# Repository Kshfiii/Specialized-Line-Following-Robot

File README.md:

# Specialized-Line-Following-Robot

This is a specialized line follower robot with a custom built 8 Sensor Array, using tcrt5000 IR sensors, for sensing the lines. In addition to basic line following, the robot has a specialized function for dispensing pellets into designated spots, at different heights, for which it uses a scissor lift along with a conveyor belt system, powered by high torque n20 motors. It was made to compete in a robotics competition, NERC, and as a way to challenge myself to make a better LFR then the one I made before, which I think I have.

## About

<!-- This Project is powered by an 11.1v 3300 mah Li-po battery. It has 3 power rails; 11.1v, 5v, and <!- 3rd power line here ->, it uses two mini mp2307 to convert the voltages.-->
### 1. Robot function 

The robot follows a 3cm wide black line on the arena floor, maneuvering intersections & Zig Zag patterns on the arena floor. At Storage rack 1 (S1), a box of 7x7 inches supports the storage rack, with one of four faces colored blue. the robot must go around the box to detect the blue colored face, where the slot openings are present in the form of a 2x2 grid, as seen in the image above. The robot must detect strips below the slots as either blue or red, placing the pellets into the slots marked blue, and skipping over the red ones. The robot then heads to Storage rack 2 (S2), repeating the same procedure. Then, the robot travels through the zig zag pattern and climbs a ramp to reach Storage rack 3 (S3), After sucessful dispensing into designated slots at S3, it parks itself beyond the red line. 

### 2. Body
The body consists of three layers. The Base, the Middle, and the top most layer. 
 #### 2.1 The Base

The base is made of a custom 3d printed Chasis, housing four GA25-370 Motors and a battery on top with the IR Sensor Array Mounted to the bottom, Alongside extruded platforms for inserts.

##### 2.1.1 IR Sensor Array

<!-- add ss of 3d model from kicad & schematics-->
A custom built 8 channel analog IR sensor array bulit from tcrt5000 sensors. It uses 4.7k & 1k resistors. It also utilizes capacitors & an led that lights up when a sensor is returning a reading, serving as a checker to see if it works. 

#### 2.2 The Middle layer

<!-- add ss of middle layer from onshape, make a banner thing with lables in canva and put it here, layer has, acrylic base, spacers, pcb, hcsr04  -->
The Middle layer is supported by a laser cut acrylic sheet which is screwed on top of the 3d printed chasis using spacers. It consists of a custom built PCB & spacers along with the HC-SR04 ultrasonic sensor for distance measurement. 

##### 2.2.1 PCB

The pcb routes a 3300mah, 11.1v li-po battery pack through two mini MP2307 buck convertor, forming 3 power rails, 11.1v, 5v, and <!-- x volts --> which are used throughout the robot. The PCB houses the STM32F401 Microcontroller with two TB6612FNG motor driver breakout boards, one of which governs the motion of the GA25-370 motors and the other controls the N20 motors used for raising the scissor lift and moving the conveyor belt. It has headers for the IR sensors and the ultrasonic sensor.

#### 2.3 The Top layer

The top layer is also supported by a laser cut acrylic sheet which is screwed on top of the first acrylic sheet, separated by ~1.2in vertically, using spacers and nuts. It is home to the whole Pellet dispensing mechanism, The scissor lift, the Color sensing system and the conveyor belt.

##### 2.3.1 Scissor lift
<!-- add ss of 3d model from onshape, make a banner thing with lables in canva and put it here -->
The scissor lift is made entriely of a 3d printed body. It's movement is controlled by a high torque N20 gear motor which sits on the acrylic sheet. The collapsed height of the lift is <!-- x inches --> and it can streatch upto <!-- y inches --> 

##### 2.3.2 Color sensing system
<!-- add ss of 3d model from onshape, make a banner thing with lables in canva and put it here -->
The color sensing system consists of a Sg90 servo with a TCS34725 color sensor mounted to a 3d printed arm, which is screwed onto Sg90. The arm is <!-- z inches --> in length. The system is fixed underneath the top plate of the scissor lift, so that it can climb with the lift, giving it the ability to detect the color of the strips at both heights vertically. The servo rotates the arm 180° which allows the color sensor to detect both heights laterally. By using this system, the color sensor can cover the strips below each slot in the 2x2 grid.

##### 2.3.3 Conveyor belt
<!-- add ss of 3d model from onshape with the pellets stored and dimensions, make a banner thing with lables in canva and put it here -->
The conveyor belt is made of a 3d printed body. It uses a high torque N20 motor and bearings to rotate the pulleys, which drive the belt. The pellets sit on top of the belt, preloaded before the robot starts. 

## Assembly & Building
Go to [Onshape](https://cad.onshape.com/documents/1d0c454716dc1fb7909d87f9/w/77de741c5d18967e566ddcde/e/cc4241ede1b87dd95ef516c6?renderMode=0&uiState=6a198c15967ad61ab2482240) Each part of the Line follower robot has been organized into folders. All print parts are consolidated in the 'To Print' tab on the bottom left. If confusion persists, you may contact me at: kasshafemman@gmail.com. Now follow along for each section.

### Body
Open the LFR Body Folder to see the CAD model. Now, using the brackets, fix the motors to the chasis. Put the wheels on the motor shaft. Put the insrts into the extruded square, then use it to screw Acrylic layer one. Put the PCB on this layer and the Ultrasonic sensor, within its bracket. Add a spacer and screw in Acrylic layer 2. Then put the scissor lift's extruded patterns (for the lack of a better word) on top of the complimentary slots on Acrylic layer 2.

### Scissor Lift:
Open Scissor lift folder for reference. Slide the scissor legs onto the shafts and put them in the place holders made on platform one. Use a string or pice of yarn, tying one end to the n20 motor and the other to the center of shaft 2. To prevent the shafts from sliding off, attach the knubs to the shaft's complementery ends. Now put pin 1 through one end of the hole in the scissor leg and pin 2 through the other, repeat this for all the arms to get the scissors pattern as shown in the assembly.

### Conveyor Belt
Open conveyor belt folder for reference. Put the supports into side plate 1 of the conveyor belt. Glue in bearings in the holes of both plates and put the pulleys inside the bearings. Now attach Side plate 2 on the other side. Put the conveyor belt onto the scissor lift, which had complementary holes to have it fixed in place.

## Robot Logic & Software
It is written in C++ using the Arduino framework on an STM32F401 (Black Pill). The code is split into six files, 'drive', 'sensors', 'Lift', 'nav' (short for navigation', 'pellet dispension' (color sensing + conveyor belt), with each of them handling one specific robot fuction, plus an additional 'config.h' where I put the tunable values.

Navigation is handled by the nav.cpp file, which uses a PID logic and values from the IR sensor array to stay on the line. The Wheel encodersb give additional feedback, measuring the distance traveled, and the HC-SR04 ultrasonic sensor confirms when the robot is close enough to a rack for dispensing.

At each station, the robot scans the rack using the color sensing mechanism. The TCS34725 is aligned so that it faces the colored strip. It takes several readings at its position, so that it can detect the color of the strip reliably. If the strip is blue, the robot alligns itself with the rack and a pellet is dispensed. After that, the servo rotates 180°, sensing the other strip laterally. The process is repeated for both the lower and upper rows of the rack, the lift raises the sensor and dispenser to reach the upper row. Additionally, Color readings are normalized to reduce the effect of changing lighting conditions.

The robot follows the black line, navigating to S1, dropping the pellets, Then repeating the same for S2, then climbs the ramp to S3, drops the pellets and parks itself beyond the finsih line. `nav.cpp` handles line following using a PID controller on the IR array's weighted error, with encoder ticks tracking distance from the last known point and the HC-SR04 confirming when the rack face is actually in range.

The servicing routine is the same for all three units. The robot closes in on the rack, sweeps the color sensor servo left and right at the lower row, reads the TCS34725 five times per position, nudges left or right and ejects into whichever slots came back blue, then raises the lift and repeats for the upper row. Color detection normalizes against the clear channel so arena lighting doesn't throw it off.

### Dependencies
To work, the firmware needs:
- STM32duino core
- `Adafruit_TCS34725` via Arduino Library Manager
- `Wire` and `Servo` ship with the core

## Component List
1. STM32F401 (Blackpill) Microcontroller
2. B6612FNG Motor Driver
3. JGA25-370 Motor with wheels and Brackets
4. TCRT5000 IR sensors
5. Resistors and capacitors
6. 11.1v 3300mAh Lipo Battery
7. High torque N20 Motors
8. TCS34725 Color Sensor
9. Hc-sr04 Ultrasonic Sensor
10. Bearings
11. Acrylic sheet

## Bill of Materials
| Component | Quantity | Est. Cost (USD) | Purchase Links | 
| :--- | :---: | :--- | :--- | 
| **PLA Filament**| 1 | $16.55 |[Link](https://electrobes.com/product/exyz-pla-1-75mm-3d-printer-filament-1kg-roll/)| 
| **11.1v 3300mAh Lipo Battery** | 1 | $24.00 | [Link](https://colgroad.com/product/zop-power-3s-11-1v-3300mah-25c-lipo-battery/) | 
| **JGA25-370 Motor kit** | 4 | $48.00 | [Link](https://colgroad.com/product/dc-gear-motor-with-encoder-280rpm-620rpm-ga25-370-complete-kit/)| 
| **TCRT5000 IR sensors** | 10 | $03.40 |[Link](https://epro.pk/product/tcrt5000-reflective-optical-ir-sensor-in-pakistan/)| 
| **Resistors** | 2 | $00.50 |[Link](https://epro.pk/product/1206-smd-resistor-smd-1206-tolerance-5-smd-resistor-1206-pack-of-10-pcs-2/?attribute_pa_1206-resistance-value=4r7)| 
| **SMD LED** | 2 | $00.75 |[Link](https://digilog.pk/products/100pcs-smd-0805-led-smt-led-light-diode?variant=49762233876758)| 
| **Hc-sr04 Ultrasonic Sensor** | 1 | $00.72 | [Link](https://epro.pk/product/ultrasonic-sensor-hc-sr04-in-pakistan/) | 
| **Standoff** | 2 | $00.25 |[Link](https://epro.pk/product/brass-standoff-spacer-screw-long-pillars-nut/)| 
| **Mp2307 Buck convertor** | 2 | $00.90 |[Link](https://epro.pk/product/dc-to-dc-step-down-mini-360-buck-converter-module/)| 
| **6 pin Jst-xh connector** | 4 | $00.14 |[Link](https://digilog.pk/products/6-pin-2-5mm-jst-xh-style-male-connector-in-pakistan)| 
| **Xt60 Lipo battery connector** | 1 | $00.65 |[Link](https://epro.pk/product/xt60connectorsmalefemalepairinpakistan/)| 
| **Sg90 Servo Motor** | 1 | $1.15 |[Link](https://epro.pk/product/tower-pro-sg90-9g-micro-servo-motor-with-accessories-blue/)| 
| **STM32F401**| 1 | $03.55 |[Link](https://epro.pk/product/stm32f401-development-board/)| 
| **TB6612FNG Motor Driver**| 1 | $02.00 | [Link](https://epro.pk/product/tb6612-drv8833-dual-motor-driver-module-1a-h-bridge-for-arduino-robotics/) | 
| **200 RPM N20 Motors** | 2 | $03.00 | [Link](https://colgroad.com/product/n20-mini-dc-gear-motor-200-600-800-1000-rpm-brand-new/) | 
| **TCS34725 Color Sensor** | 1 | $03.58 | [Link](https://digilog.pk/products/tcs34725-color-sensor-module-pakistan) | 
| **Bearings** | 1 | $4.30 | [Link](https://epro.pk/product/cnc-v-slot-bearing-open-builds-wheel-pom-mr105zz-625zz-bore-5mm-passive-round-gear/) | 
| **Acrylic sheet** | 2 | $03.23 | [Link](https://www.daraz.pk/products/acrylic-sheet-2mm-size-12x12-2mm-thick-i391245284.html)| 
| **Total Build Cost:** |  | **~$120.00** |

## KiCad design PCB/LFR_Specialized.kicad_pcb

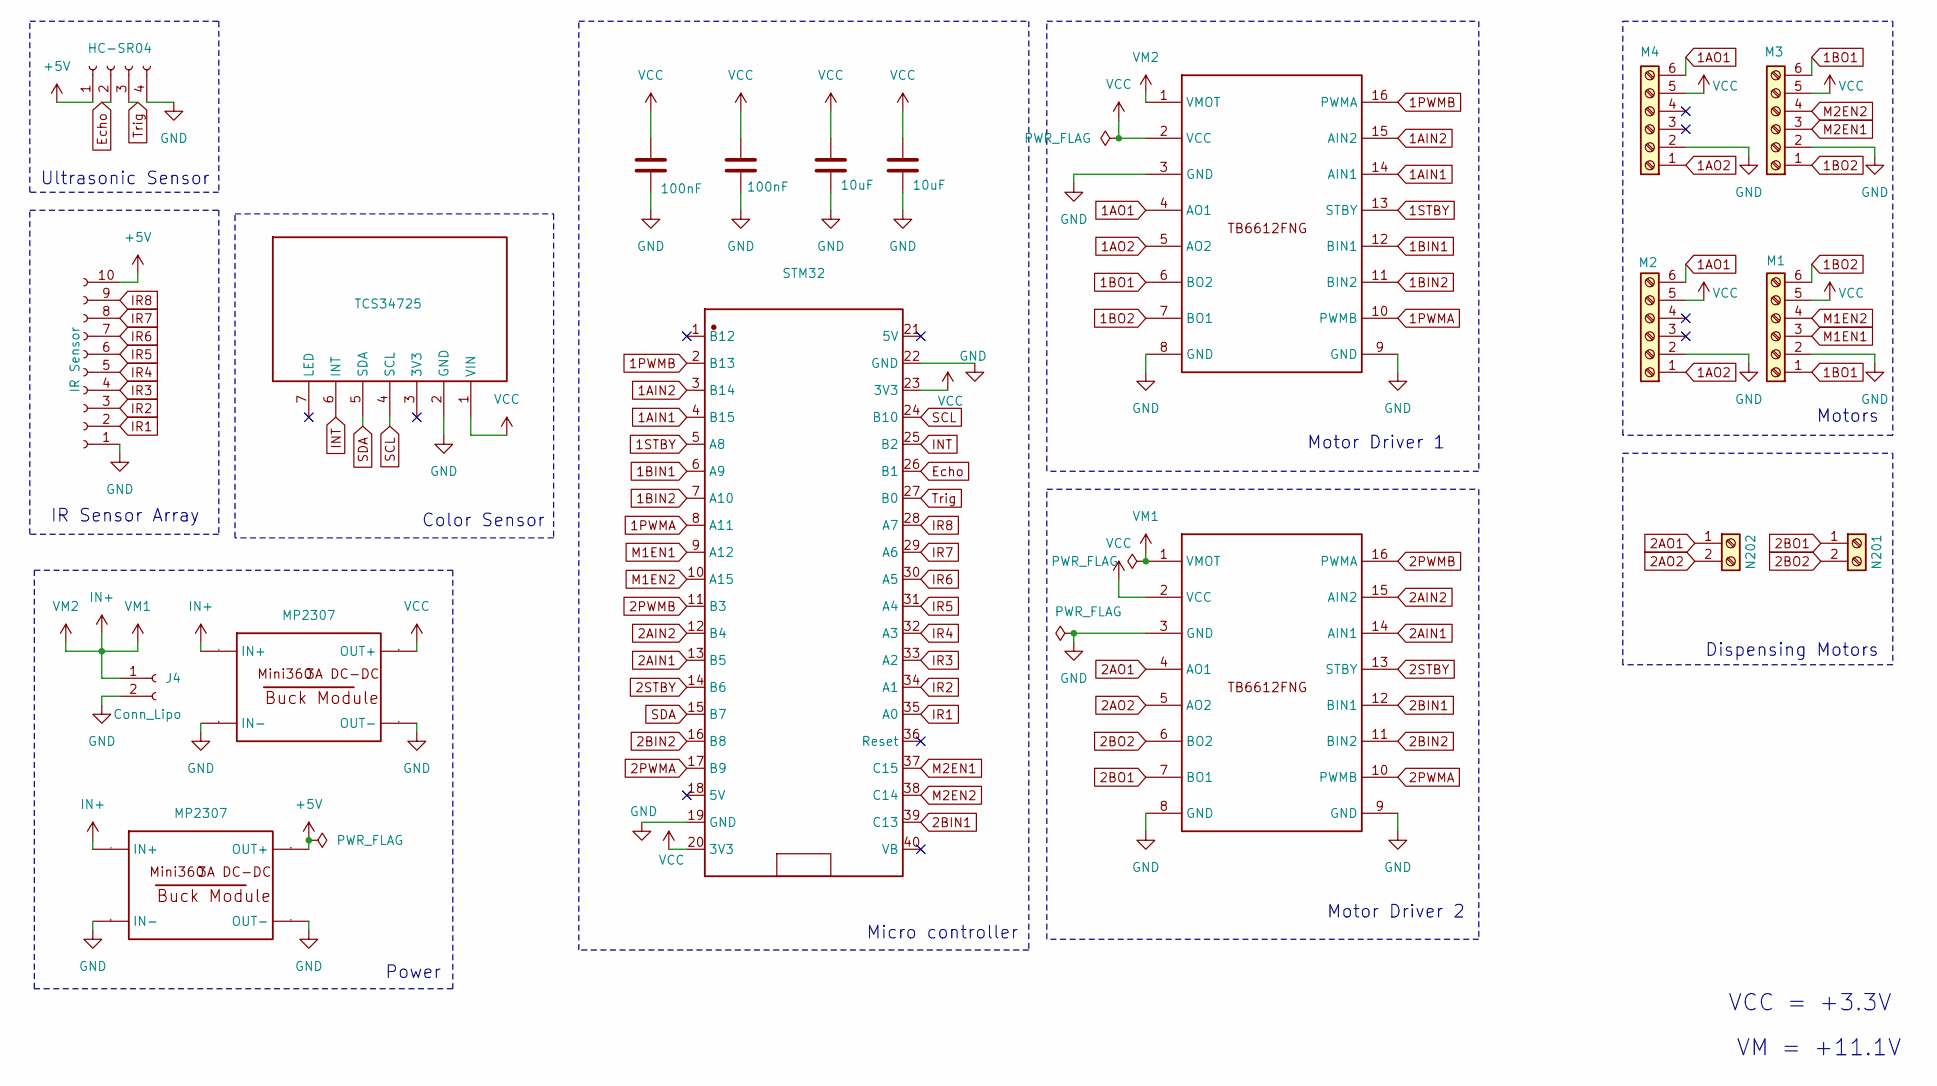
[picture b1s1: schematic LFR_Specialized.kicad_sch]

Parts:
C1, C12: 10uF; C_Disc_D5.0mm_W2.5mm_P2.50mm
C9, C11: 100nF; C_Disc_D5.0mm_W2.5mm_P2.50mm
J2: M1; JST_PH_B6B-PH-K_1x06_P2.00mm_Vertical
J3: M2; JST_PH_B6B-PH-K_1x06_P2.00mm_Vertical
J4: Conn_Lipo; AMASS_XT60-M_1x02_P7.20mm_Vertical
J5: N201; terminal
J6: N202; terminal
J7: HC-SR04; PinHeader_1x04_P2.54mm_Vertical
J8: M4; JST_PH_B6B-PH-K_1x06_P2.00mm_Vertical
J9: IR Sensor; PinHeader_1x10_P2.54mm_Vertical
J10: M3; JST_PH_B6B-PH-K_1x06_P2.00mm_Vertical
P1: TCS34725; PinHeader_1x07_P2.54mm_Vertical
STM32: STM32F401CC-WEACTBOARD-FOOTPRINT
U1, U3: TB6612FNG Dual Motor Driver SparkFun; TB6612FNG-BREAKOUT
U2, U4: MP2307; MINI360 BUCK CONVERTOR

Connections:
1AIN1: STM32.4 (B15), U3.14 (AIN1)
1AIN2: STM32.3 (B14), U3.15 (AIN2)
1AO1: J3.6, J8.6, U3.4 (AO1)
1AO2: J3.1, J8.1, U3.5 (AO2)
1BIN1: STM32.6 (A9), U3.12 (BIN1)
1BIN2: STM32.7 (A10), U3.11 (BIN2)
1BO1: J2.1, J10.6, U3.6 (BO2)
1BO2: J2.6, J10.1, U3.7 (BO1)
1PWMA: STM32.8 (A11), U3.10 (PWMB)
1PWMB: STM32.2 (B13), U3.16 (PWMA)
1STBY: STM32.5 (A8), U3.13 (STBY)
2AIN1: STM32.13 (B5), U1.14 (AIN1)
2AIN2: STM32.12 (B4), U1.15 (AIN2)
2AO1: J6.1, U1.4 (AO1)
2AO2: J6.2, U1.5 (AO2)
2BIN1: STM32.39 (C13), U1.12 (BIN1)
2BIN2: STM32.16 (B8), U1.11 (BIN2)
2BO1: J5.1, U1.7 (BO1)
2BO2: J5.2, U1.6 (BO2)
2PWMA: STM32.17 (B9), U1.10 (PWMB)
2PWMB: STM32.11 (B3), U1.16 (PWMA)
2STBY: STM32.14 (B6), U1.13 (STBY)
Echo: J7.2, STM32.26 (B1)
GND: C1.2, C9.2, C11.2, C12.2, J2.2, J3.2, J4.2, J7.4, J8.2, J9.1, J10.2, P1.2 (GND), STM32.19 (GND), STM32.22 (GND), U1.3 (GND), U1.8 (GND), U1.9 (GND), U2.1 (IN-), U2.3 (OUT-), U3.3 (GND), U3.8 (GND), U3.9 (GND), U4.1 (IN-), U4.3 (OUT-)
IN+: J4.1, U1.1 (VMOT), U2.2 (IN+), U3.1 (VMOT), U4.2 (IN+)
INT: P1.6 (INT), STM32.25 (B2)
IR1: J9.2, STM32.35 (A0)
IR2: J9.3, STM32.34 (A1)
IR3: J9.4, STM32.33 (A2)
IR4: J9.5, STM32.32 (A3)
IR5: J9.6, STM32.31 (A4)
IR6: J9.7, STM32.30 (A5)
IR7: J9.8, STM32.29 (A6)
IR8: J9.9, STM32.28 (A7)
M1EN1: J2.3, STM32.9 (A12)
M1EN2: J2.4, STM32.10 (A15)
M2EN1: J10.3, STM32.37 (C15)
M2EN2: J10.4, STM32.38 (C14)
SCL: P1.4 (SCL), STM32.24 (B10)
SDA: P1.5 (SDA), STM32.15 (B7)
Trig: J7.3, STM32.27 (B0)

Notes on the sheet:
VM = +11.1V
Ultrasonic Sensor
Power
Dispensing Motors
Motors
Micro controller
Motor Driver 2
Color Sensor
IR Sensor Array
Motor Driver 1
VCC = +3.3V

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
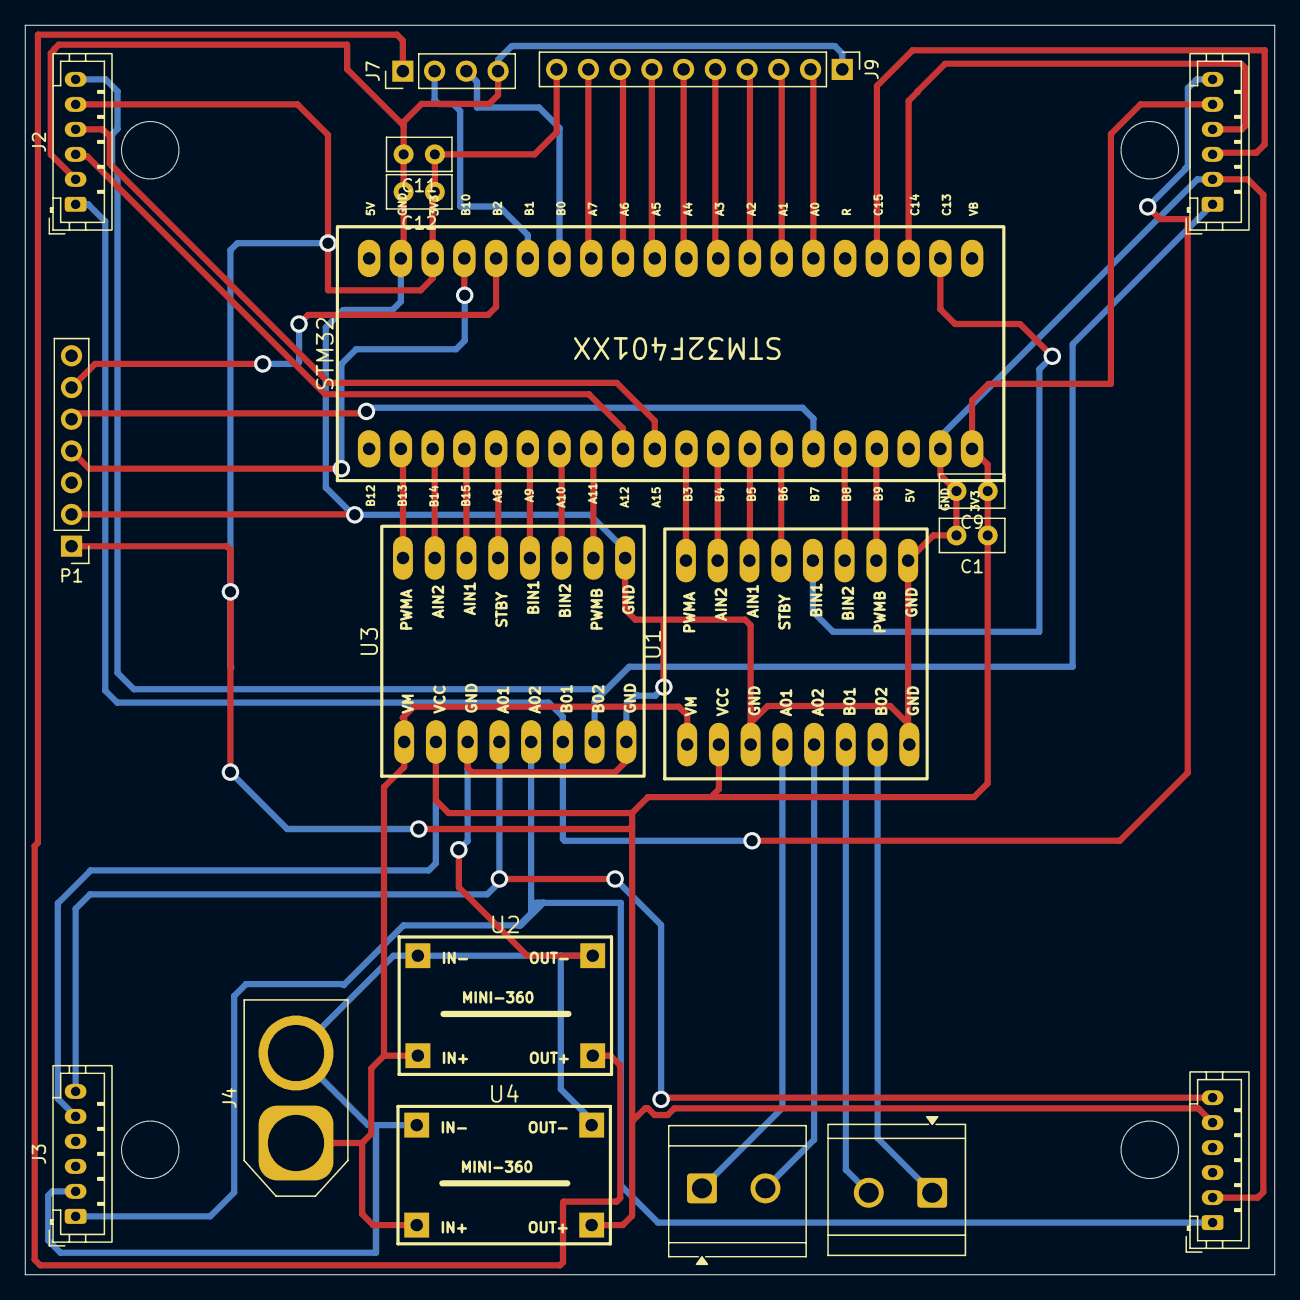
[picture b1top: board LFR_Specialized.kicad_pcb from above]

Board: 2 copper layers, 100.0 x 100.0 mm, 19 parts (0 on the bottom side), 43 nets.

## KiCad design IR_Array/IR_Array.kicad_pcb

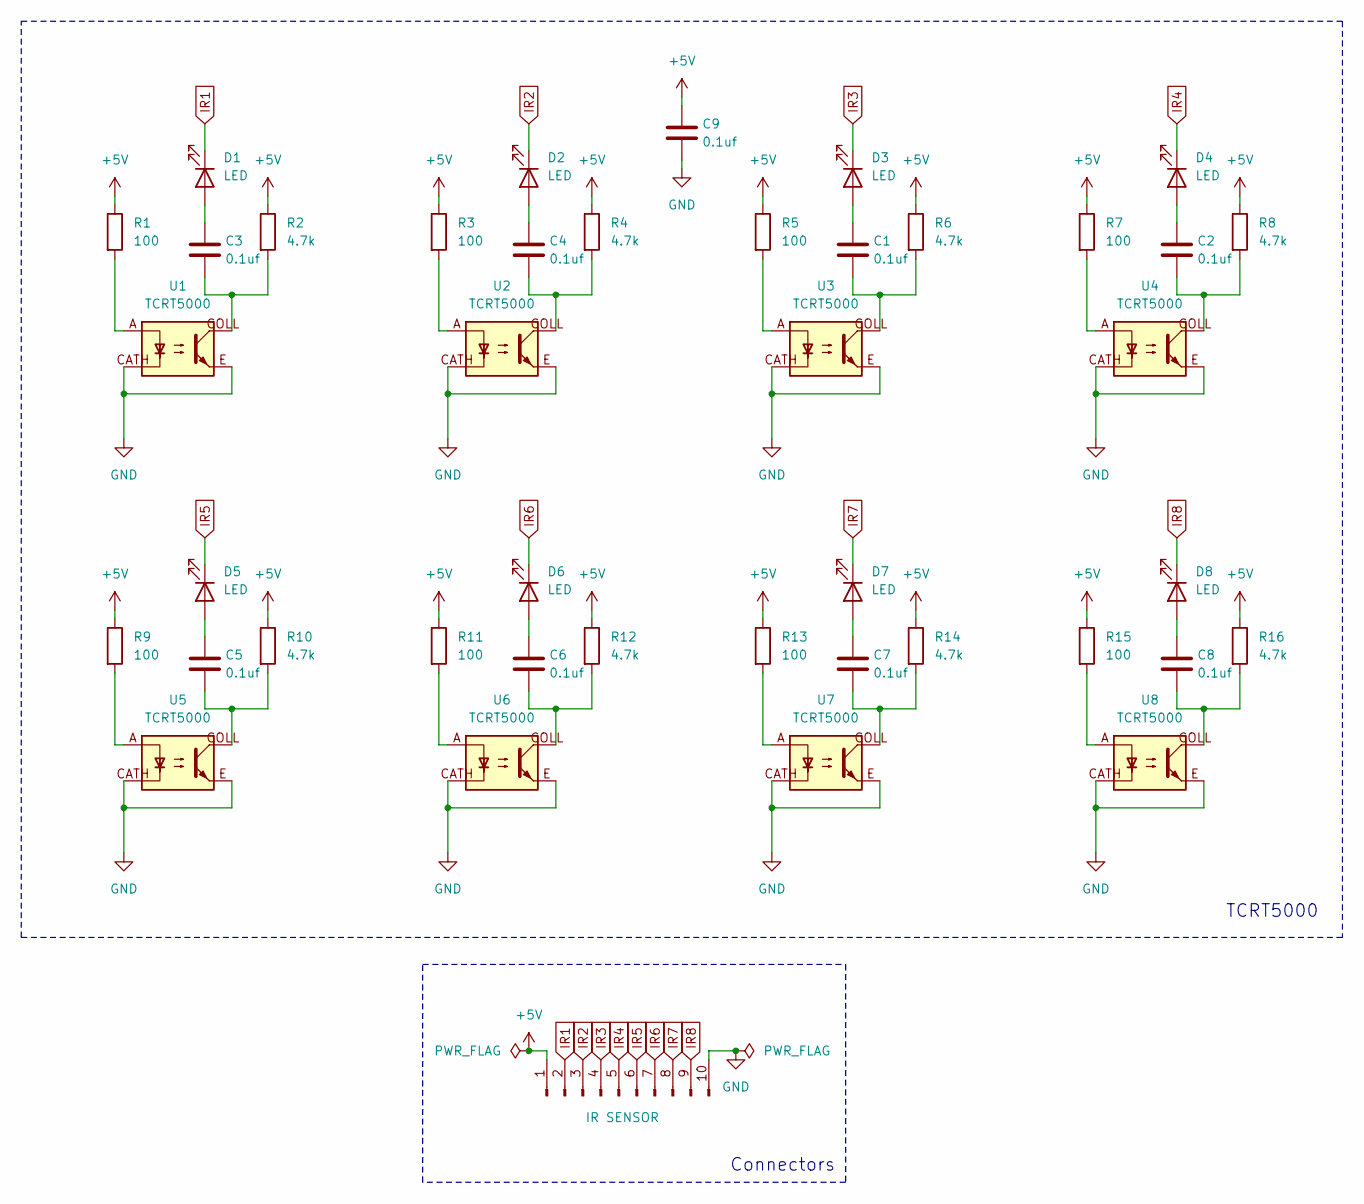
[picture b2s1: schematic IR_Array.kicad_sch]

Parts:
C1, C2, C3, C4, C5, C6, C7, C8, C9: 0.1uf; C_1206_3216Metric_Pad1.33x1.80mm_HandSolder
D1, D2, D3, D4, D5, D6, D7, D8: LED; LED_1206_3216Metric_Pad1.42x1.75mm_HandSolder
J1: IR SENSOR; PinHeader_1x10_P2.54mm_Vertical
R1, R3, R5, R7, R9, R11, R13, R15: 100; R_1206_3216Metric_Pad1.30x1.75mm_HandSolder
R2, R4, R6, R8, R10, R12, R14, R16: 4.7k; R_1206_3216Metric_Pad1.30x1.75mm_HandSolder
U1, U2, U3, U4, U5, U6, U7, U8: TCRT5000; tcrt5000

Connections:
+5V: C9.1, J1.1, R1.1, R2.1, R3.1, R4.1, R5.1, R6.1, R7.1, R8.1, R9.1, R10.1, R11.1, R12.1, R13.1, R14.1, R15.1, R16.1
GND: C9.2, J1.10, U1.CATH, U1.E, U2.CATH, U2.E, U3.CATH, U3.E, U4.CATH, U4.E, U5.CATH, U5.E, U6.CATH, U6.E, U7.CATH, U7.E, U8.CATH, U8.E
IR1: D1.1 (K), J1.2
IR2: D2.1 (K), J1.3
IR3: D3.1 (K), J1.4
IR4: D4.1 (K), J1.5
IR5: D5.1 (K), J1.6
IR6: D6.1 (K), J1.7
IR7: D7.1 (K), J1.8
IR8: D8.1 (K), J1.9
unnamed: C1.2, R6.2, U3.COLL
unnamed: C2.2, R8.2, U4.COLL
unnamed: C3.2, R2.2, U1.COLL
unnamed: C4.2, R4.2, U2.COLL
unnamed: C5.2, R10.2, U5.COLL
unnamed: C6.2, R12.2, U6.COLL
unnamed: C7.2, R14.2, U7.COLL
unnamed: C8.2, R16.2, U8.COLL
unnamed: C3.1, D1.2 (A)
unnamed: C4.1, D2.2 (A)
unnamed: C1.1, D3.2 (A)
unnamed: C2.1, D4.2 (A)
unnamed: C5.1, D5.2 (A)
unnamed: C6.1, D6.2 (A)
unnamed: C7.1, D7.2 (A)
unnamed: C8.1, D8.2 (A)
unnamed: R1.2, U1.A
unnamed: R3.2, U2.A
unnamed: R5.2, U3.A
unnamed: R7.2, U4.A
unnamed: R9.2, U5.A
unnamed: R11.2, U6.A
unnamed: R13.2, U7.A
unnamed: R15.2, U8.A

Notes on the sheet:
Connectors
TCRT5000

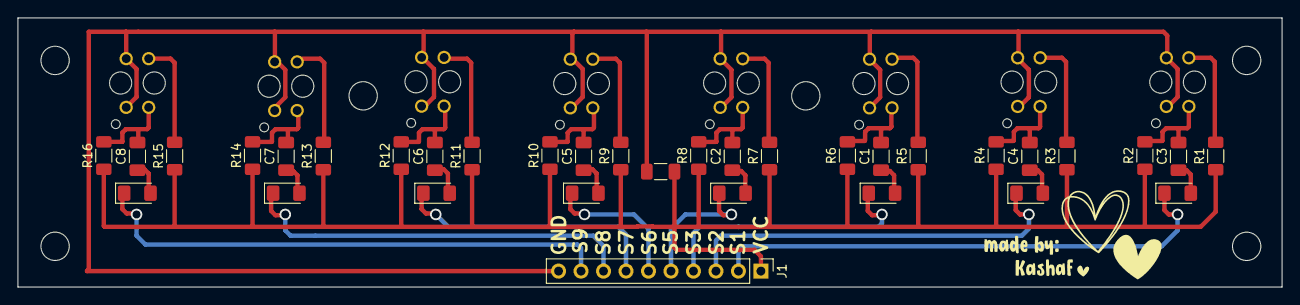
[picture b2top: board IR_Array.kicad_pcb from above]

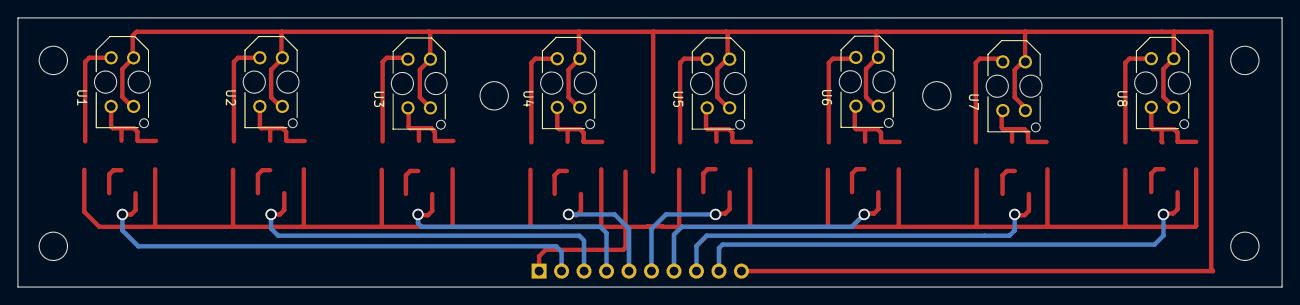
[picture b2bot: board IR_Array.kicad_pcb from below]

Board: 2 copper layers, 142.8 x 30.4 mm, 42 parts (8 on the bottom side), 34 nets.

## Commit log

2026-05-06 Update price for QTR 8C IR Sensor Array
    Updated the price of the QTR 8C IR Sensor Array from $05.00 to $04.59.
2026-05-06 Update component list and total build cost in README
2026-05-17 Update Bill of Materials with new components and costs
2026-05-27 Revise robot function description in README
    Updated the robot description for clarity and added details about storage racks and procedures.
2026-05-28 Enhance README with detailed body structure and BOM
    Expanded the body section with detailed descriptions of the robot's layers, including the base, middle, and top layers, along with their components and functionalities. Added a bill of materials for 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
2026-05-29 Enhance README with images and detailed descriptions
    Added images and expanded descriptions for robot functionality and components.
2026-05-29 Add Bill of Materials with components and costs
2026-05-29 Update BOM.csv with new formatting and links
2026-05-29 Enhance README with competition details
    Expanded project description to include competition context and personal challenge.
2026-05-30 Document robot logic and software details in README
    Added section on Robot Logic & Software detailing the C++ code structure and functionality.
2026-05-31 Update total build cost in README
